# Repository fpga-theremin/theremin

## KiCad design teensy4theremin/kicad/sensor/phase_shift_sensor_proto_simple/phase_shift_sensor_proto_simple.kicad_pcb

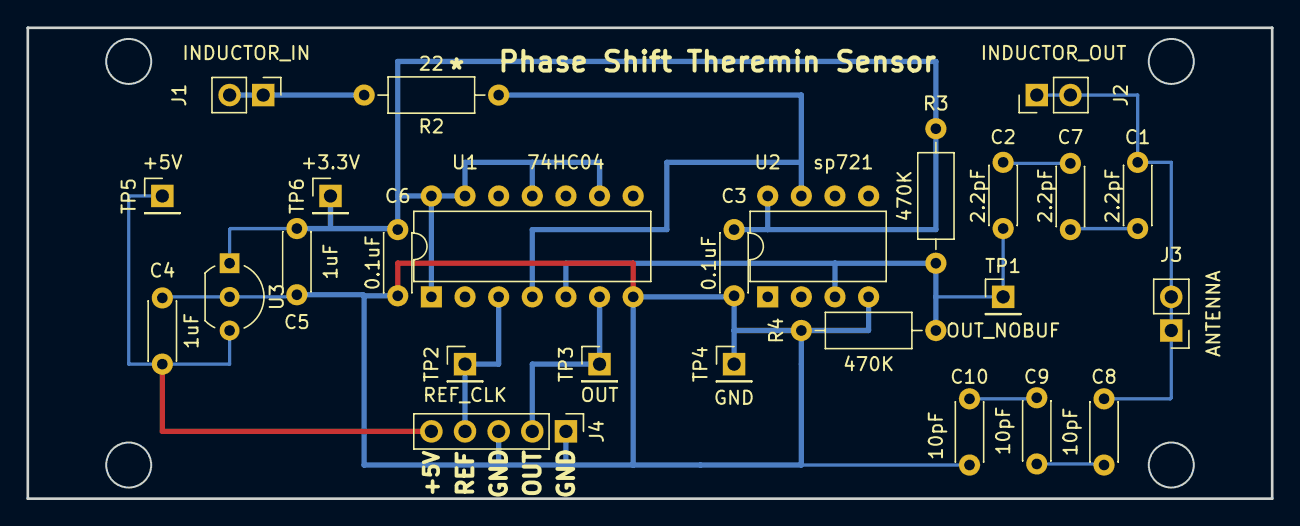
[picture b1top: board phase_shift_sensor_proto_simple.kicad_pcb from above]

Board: 2 copper layers, 94.0 x 35.6 mm, 26 parts (0 on the bottom side), 13 nets.

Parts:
C1, C2, C7: 2.2pF; C_Disc_D4.3mm_W1.9mm_P5.00mm
C3, C6: 0.1uF; C_Disc_D4.3mm_W1.9mm_P5.00mm
C4, C5: 1uF; C_Disc_D4.3mm_W1.9mm_P5.00mm
C8, C9, C10: 10pF; C_Disc_D4.3mm_W1.9mm_P5.00mm
J1: INDUCTOR_IN; PinHeader_1x02_P2.54mm_Vertical
J2: INDUCTOR_OUT; PinHeader_1x02_P2.54mm_Vertical
J3: ANTENNA; PinHeader_1x02_P2.54mm_Vertical
J4: SENSOR; PinHeader_1x05_P2.54mm_Vertical
R2: 22; R_Axial_DIN0207_L6.3mm_D2.5mm_P10.16mm_Horizontal
R3, R4: 470K; R_Axial_DIN0207_L6.3mm_D2.5mm_P10.16mm_Horizontal
TP1: OUT_NOBUF; PinHeader_1x01_P2.54mm_Vertical
TP2: REF_CLK; PinHeader_1x01_P2.54mm_Vertical
TP3: OUT; PinHeader_1x01_P2.54mm_Vertical
TP4: GND; PinHeader_1x01_P2.54mm_Vertical
TP5: +5V; PinHeader_1x01_P2.54mm_Vertical
TP6: +3.3V; PinHeader_1x01_P2.54mm_Vertical
U1: 74HC04; DIP-14_W7.62mm
U2: sp721; DIP-8_W7.62mm
U3: L78L33_TO92; TO-92_Inline_Wide

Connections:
+3V3: C3.1, C5.1, C6.1, R3.1, TP6.1, U1.1, U1.9, U1.11, U1.13, U1.14, U2.8, U3.1
+5V: C4.1, J4.5, TP5.1, U3.3
/OUT: J4.2, TP3.1, U1.6
/REF_CLK: J4.4, TP2.1, U1.3
GND: C3.2, C4.2, C5.2, C6.2, C10.1, J4.1, J4.3, R4.2, TP4.1, U1.7, U2.4, U3.2
unnamed: C1.1, C8.2, J2.1, J2.2, J3.1, J3.2
unnamed: C1.2, C7.1
unnamed: C2.1, C7.2
unnamed: C2.2, R3.2, R4.1, TP1.1, U1.5, U2.3
unnamed: C8.1, C9.2
unnamed: C9.1, C10.2
unnamed: J1.1, J1.2, R2.2
unnamed: R2.1, U1.4, U2.7

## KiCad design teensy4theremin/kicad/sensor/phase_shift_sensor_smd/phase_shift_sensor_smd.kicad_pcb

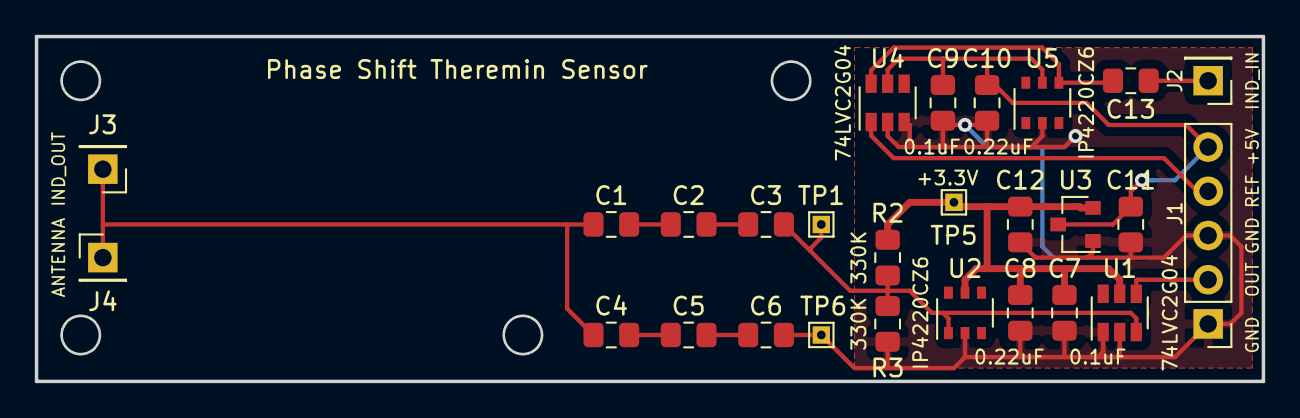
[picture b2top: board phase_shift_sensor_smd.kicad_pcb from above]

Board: 2 copper layers, 70.5 x 19.8 mm, 27 parts (0 on the bottom side), 13 nets.

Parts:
C1, C2, C3: 3.3pF; C_0805_2012Metric_Pad1.15x1.40mm_HandSolder
C4, C5, C6: 10pF; C_0805_2012Metric_Pad1.15x1.40mm_HandSolder
C7, C9, C13: 0.1uF; C_0805_2012Metric_Pad1.15x1.40mm_HandSolder
C8, C10: 0.22uF; C_0805_2012Metric_Pad1.15x1.40mm_HandSolder
C11, C12: 1uF; C_0805_2012Metric_Pad1.15x1.40mm_HandSolder
J1: SENSOR; PinHeader_1x05_P2.54mm_Vertical
J2: INDUCTOR_IN; PinHeader_1x01_P2.54mm_Vertical
J3: INDUCTOR_OUT; PinHeader_1x01_P2.54mm_Vertical
J4: ANTENNA; PinHeader_1x01_P2.54mm_Vertical
R2, R3: 330K; R_0805_2012Metric_Pad1.15x1.40mm_HandSolder
TP1: OUT_NOBUF; TestPoint_THTPad_1.0x1.0mm_Drill0.5mm
TP5: +3.3V; TestPoint_THTPad_1.0x1.0mm_Drill0.5mm
TP6: GND; TestPoint_THTPad_1.0x1.0mm_Drill0.5mm
U1, U4: 74LVC2G04; SOT-23-6
U2, U5: IP4220CZ6; TSOP-6_1.65x3.05mm_P0.95mm
U3: MCP1700-3302E_SOT23; SOT-23

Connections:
+3V3: C7.1, C8.1, C12.1, R2.1, TP5.1, U1.5, U2.5, U3.2
+5V: C9.1, C10.1, C11.1, J1.5, U3.3, U4.5, U5.5
/OUT: J1.2, U1.4
/REF_CLK: J1.4, U4.1
GND: C6.2, C7.2, C8.2, C9.2, C10.2, C11.2, C12.2, J1.1, J1.3, R3.2, TP6.1, U1.1, U1.2, U2.2, U3.1, U4.2, U4.3, U5.2
unnamed: C1.1, C4.1, J3.1, J4.1
unnamed: C1.2, C2.1
unnamed: C2.2, C3.1
unnamed: C3.2, R2.2, R3.1, TP1.1, U1.3, U2.1
unnamed: C4.2, C5.1
unnamed: C5.2, C6.1
unnamed: C13.1, J2.1
unnamed: C13.2, U4.6, U5.4

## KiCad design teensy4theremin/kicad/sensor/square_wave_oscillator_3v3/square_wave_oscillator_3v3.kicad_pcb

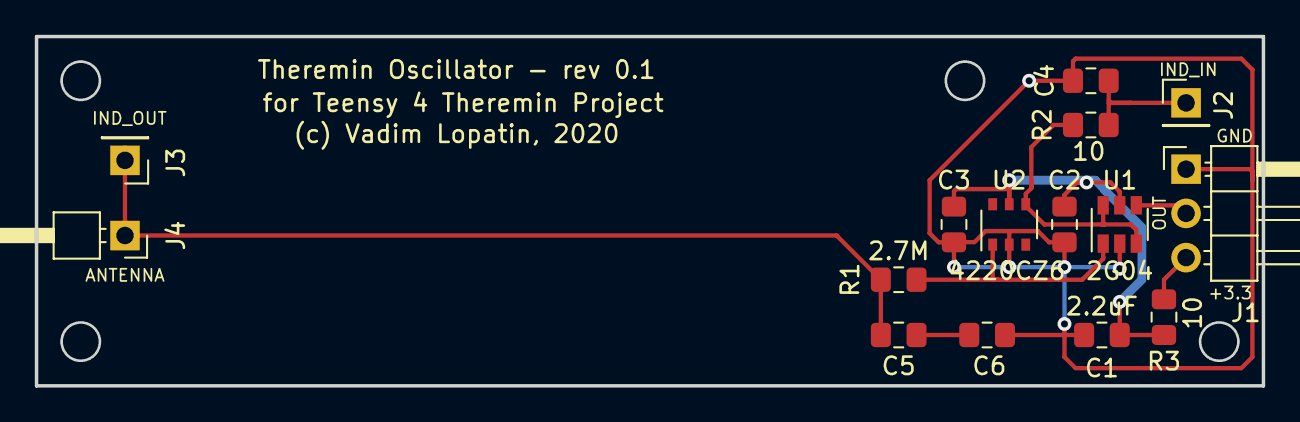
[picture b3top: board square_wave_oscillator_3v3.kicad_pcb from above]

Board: 2 copper layers, 70.5 x 20.1 mm, 15 parts (0 on the bottom side), 9 nets.

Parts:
C1: 2.2uF; C_0805_2012Metric_Pad1.15x1.40mm_HandSolder
C2: 0.1uF; C_0805_2012Metric_Pad1.15x1.40mm_HandSolder
C3: 0.22uF; C_0805_2012Metric_Pad1.15x1.40mm_HandSolder
C4, C5, C6: 3.3pF; C_0805_2012Metric_Pad1.15x1.40mm_HandSolder
J1: OSC; PinHeader_1x03_P2.54mm_Horizontal
J2: INDUCTOR_IN; PinHeader_1x01_P2.54mm_Vertical
J3: INDUCTOR_OUT; PinHeader_1x01_P2.54mm_Vertical
J4: ANTENNA; PinHeader_1x01_P2.54mm_Horizontal
R1: 2.7M; R_0805_2012Metric_Pad1.15x1.40mm_HandSolder
R2, R3: 10; R_0805_2012Metric_Pad1.15x1.40mm_HandSolder
U1: 2G04; SOT-23-6
U2: 4220CZ6; TSOP-6_1.65x3.05mm_P0.95mm

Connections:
+3V3: C1.1, C2.1, C3.1, R3.2, U1.5, U2.5
/3.3V: J1.3, R3.1
/OSC_OUT: J1.2, U1.4
GND: C1.2, C2.2, C3.2, C4.1, C6.1, J1.1, U1.2, U2.2
unnamed: C4.2, J2.1, R2.1
unnamed: C5.1, C6.2
unnamed: C5.2, J3.1, J4.1, R1.2
unnamed: R1.1, U1.1, U2.1
unnamed: R2.2, U1.3, U1.6, U2.4

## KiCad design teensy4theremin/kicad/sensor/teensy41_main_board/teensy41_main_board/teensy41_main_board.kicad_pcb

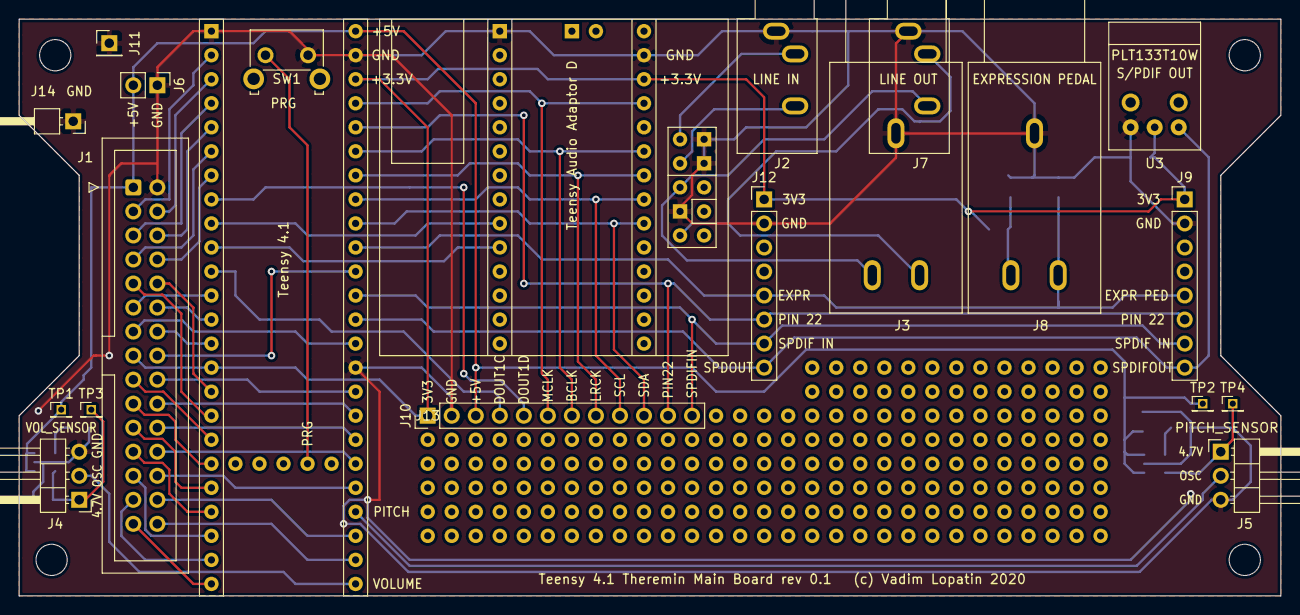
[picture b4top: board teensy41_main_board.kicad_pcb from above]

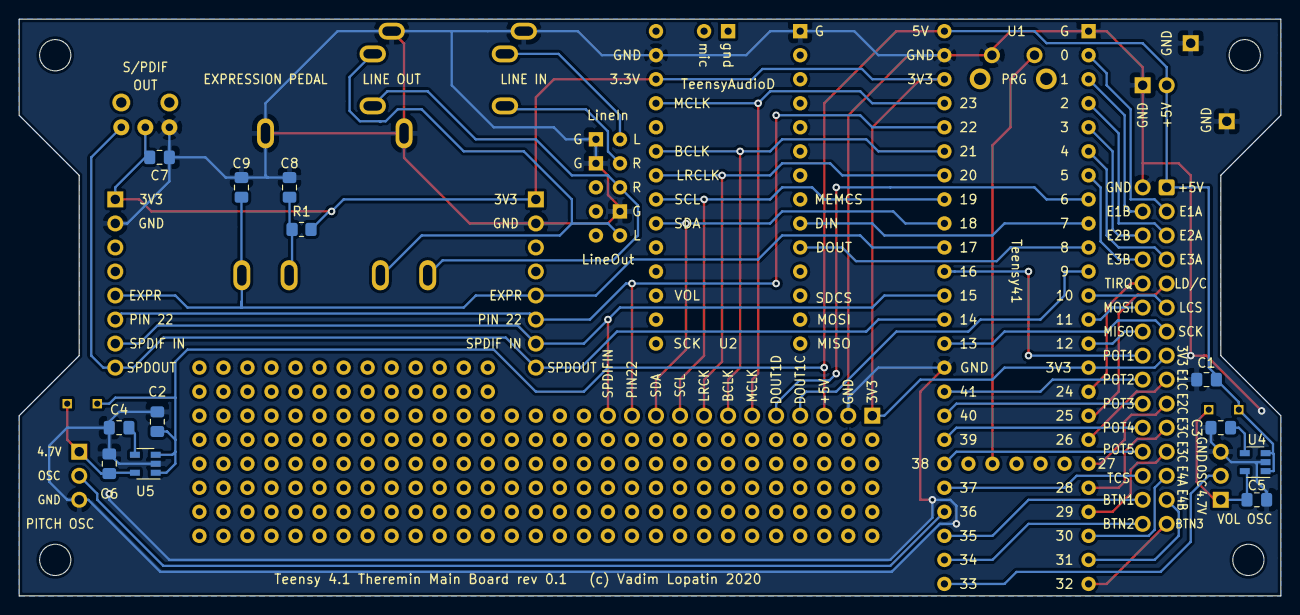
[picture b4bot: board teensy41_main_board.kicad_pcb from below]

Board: 2 copper layers, 133.3 x 61.0 mm, 34 parts (12 on the bottom side), 55 nets.

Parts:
C1, C2, C5, C6: 1uF; C_0805_2012Metric_Pad1.18x1.45mm_HandSolder
C3, C4: 10nF; C_0805_2012Metric_Pad1.18x1.45mm_HandSolder
C7, C8, C9: 0.1uF; C_0805_2012Metric_Pad1.18x1.45mm_HandSolder
J1: LCD_CONTROLS; IDC-Header_2x15_P2.54mm_Vertical
J2: LINE_IN; Jack_3.5mm_CUI_SJ1-3533NG_Horizontal
J3: LINE_OUT_BIG; Jack_6.35mm_ST_008G_04
J4: VOL_SENSOR; PinHeader_1x03_P2.54mm_Horizontal
J5: PITCH_SENSOR; PinHeader_1x03_P2.54mm_Horizontal
J6: POWER_IN; PinHeader_1x02_P2.54mm_Vertical
J7: LINE_OUT_35; Jack_3.5mm_CUI_SJ1-3533NG_Horizontal
J8: EXPR_PED; Jack_6.35mm_ST_008G_04
J9: SPDIF_IN; PinHeader_1x08_P2.54mm_Vertical
J10: AUDIO_OUT_EXT; PinHeader_1x12_P2.54mm_Vertical
J11: Grounding; PinHeader_1x01_P2.54mm_Vertical
J12: SPDIF_IN2; PinHeader_1x08_P2.54mm_Vertical
J13: ProtoGrid; Teensy41ThereminProtoGrid
J14: Grounding2; PinHeader_1x01_P2.54mm_Horizontal
R1: 200; R_0805_2012Metric_Pad1.20x1.40mm_HandSolder
SW1: SW_Push; SW_Tactile_SKHH_Angled
TP1: VIN1; PinHeader_1x01_P1.27mm_Vertical
TP2: VIN2; PinHeader_1x01_P1.27mm_Vertical
TP3: VCCVOL; PinHeader_1x01_P1.27mm_Vertical
TP4: VCCPITCH; PinHeader_1x01_P1.27mm_Vertical
U1: Teensy41
U2: TeensyAudioD
U3: PLT133T10W
U4, U5: LD3985M47R_SOT23; SOT-23-5

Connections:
/3V3: C7.1, J1.15, J9.1, J10.1, J12.1, R1.1, U1.15, U1.46, U2.26, U3.2
/BTN_1: J1.28, U1.27
/BTN_2: J1.30, U1.26
/BTN_3: J1.29, U1.24
/ENC1_A: J1.3, U1.2
/ENC1_B: J1.4, U1.3
/ENC1_C: J1.17, U1.18
/ENC2_A: J1.5, U1.4
/ENC2_B: J1.6, U1.5
/ENC2_C: J1.19, U1.19
/ENC3_A: J1.7, U1.6
/ENC3_B: J1.8, U1.7
/ENC3_C: J1.21, U1.20
/ENC4_A: J1.25, U1.22
/ENC4_B: J1.27, U1.23
/ENC4_C: J1.23, U1.21
/EXPR_PED: C9.1, J8.T, J9.5, J12.5, U1.39
/I2C_SCL: J10.9, U1.41, U2.21
/I2C_SDA: J10.10, U1.40, U2.20
/I2S_BCLK: J10.7, U1.43, U2.23
/I2S_DIN1: U1.10, U2.10
/I2S_DOUT1A: U1.9, U2.9
/I2S_DOUT1C: J10.4, U1.11
/I2S_DOUT1D: J10.5, U1.8
/I2S_LRCK: J10.8, U1.42, U2.22
/I2S_MCLK: J10.6, U1.45, U2.25
/LCD_CS: J1.11, U1.12
/LCD_DC: J1.9, U1.17
/LCD_MISO: J1.14, U1.14
/LCD_MOSI: J1.12, U1.13
/LCD_SCK: J1.13, U1.35
/LIN_L: J2.T, U2.29
/LIN_R: J2.R, U2.30
/LOUT_L: J3.T, J7.T, U2.33
/LOUT_R: J3.R, J7.R, U2.31
/PIN22: J9.6, J10.11, J12.6, U1.44
/PITCH_OSC: J5.2, U1.28
/POT1: J1.16, U1.38
/POT2: J1.18, U1.33
/POT3: J1.20, U1.32
/POT4: J1.22, U1.31
/POT5: J1.24, U1.30
/PROG: SW1.1, U1.52
/SPDIF_IN: J9.7, J10.12, J12.7, U1.37
/SPDIF_OUT: J9.8, J12.8, U1.36, U3.1
/TOUCH_CS: J1.26, U1.29
/TOUCH_IRQ: J1.10, U1.16
/VCC_PITCH: C6.1, J5.1, TP4.1, U5.5
/VCC_VOL: C5.1, J4.1, TP3.1, U4.5
/VIN: C1.1, C2.1, J1.1, J6.2, J10.3, TP1.1, TP2.1, U1.48, U4.1, U4.3, U5.1, U5.3
/VOL_OSC: J4.2, U1.25
GND: C1.2, C2.2, C3.2, C4.2, C5.2, C6.2, C7.2, C8.2, C9.2, J1.2, J2.S, J3.S, J4.3, J5.3, J6.1, J7.S, J8.S, J9.2, J10.2, J11.1, J12.2, J14.1, SW1.2, U1.1, U1.34, U1.47, U2.1, U2.27, U2.32, U2.37, U2.38, U3.3, U4.2, U5.2
unnamed: C3.1, U4.4
unnamed: C4.1, U5.4
unnamed: C8.1, J8.R, R1.2
